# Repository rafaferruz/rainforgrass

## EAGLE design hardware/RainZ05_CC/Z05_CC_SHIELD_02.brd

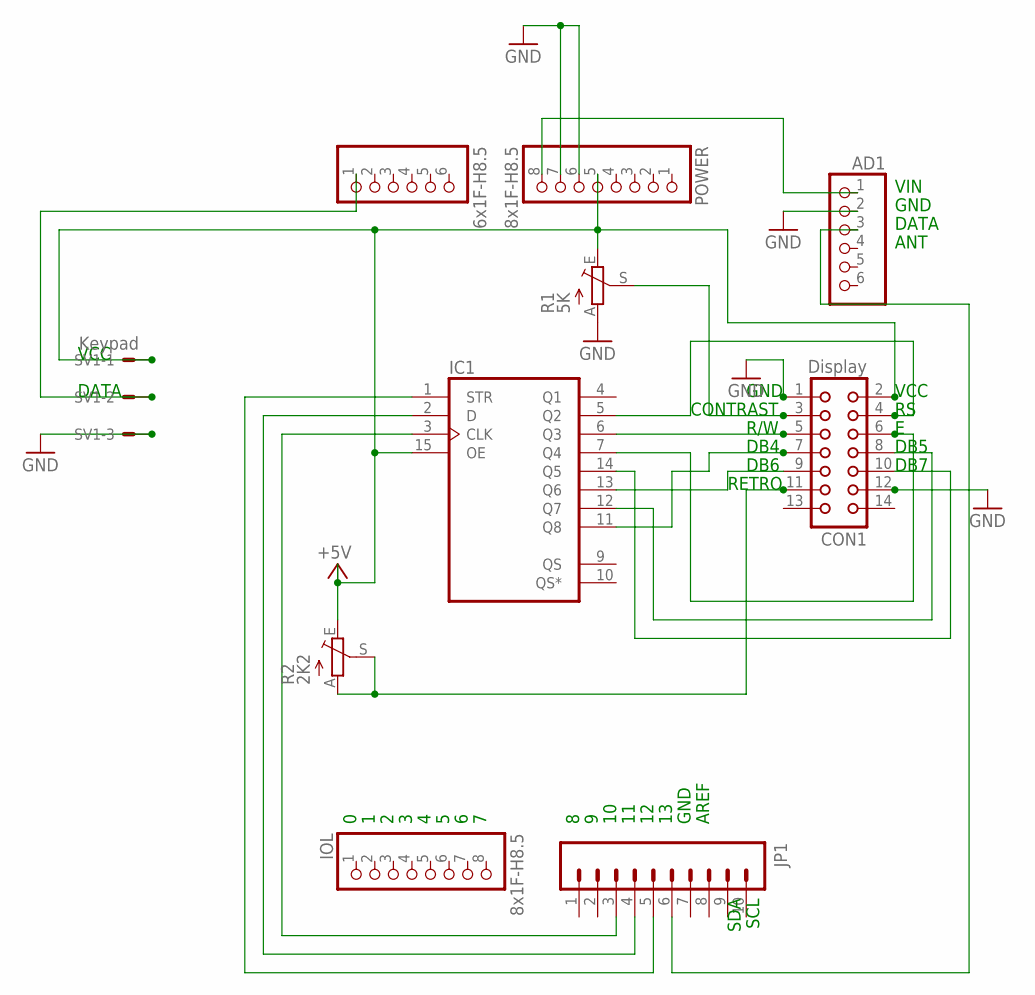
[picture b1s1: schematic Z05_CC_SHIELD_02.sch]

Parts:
AD, AD1: 6x1F-H8.5; 1X06
CON1: Display; CON14
IC1: 4094N; DIL16
IOL: 8x1F-H8.5; 1X08
JP1: M10"; 1X10
POWER: 8x1F-H8.5; 1X08
R1: 5K; LI10
R2: 2K2; LI10
SV1: Keypad; 7395-05

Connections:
+5V: CON1.2, IC1.15 (OE), POWER.5, R1.E, R2.E, SV1.1
A5: AD.1, SV1.2
GND: AD1.2, CON1.1, CON1.12, POWER.6, POWER.7, R1.A, SV1.3
unnamed: CON1.11, R2.A, R2.S
unnamed: AD1.3, JP1.6
unnamed: CON1.3, R1.S
unnamed: IC1.1 (STR), JP1.5
unnamed: IC1.2 (D), JP1.4
unnamed: IC1.3 (CLK), JP1.3
unnamed: CON1.4, IC1.5 (Q2)
unnamed: CON1.5, IC1.6 (Q3)
unnamed: CON1.6, IC1.7 (Q4)
unnamed: CON1.7, IC1.11 (Q8)
unnamed: CON1.8, IC1.12 (Q7)
unnamed: CON1.9, IC1.13 (Q6)
unnamed: CON1.10, IC1.14 (Q5)
VDD: IC1.16 (VDD)
VIN: AD1.1, POWER.8
VSS: IC1.8 (VSS)

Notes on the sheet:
SDA
SCL
GND
AREF
RETRO
VIN
DATA
ANT
VCC
CONTRAST
R/W
DB4
DB5
DB6
DB7

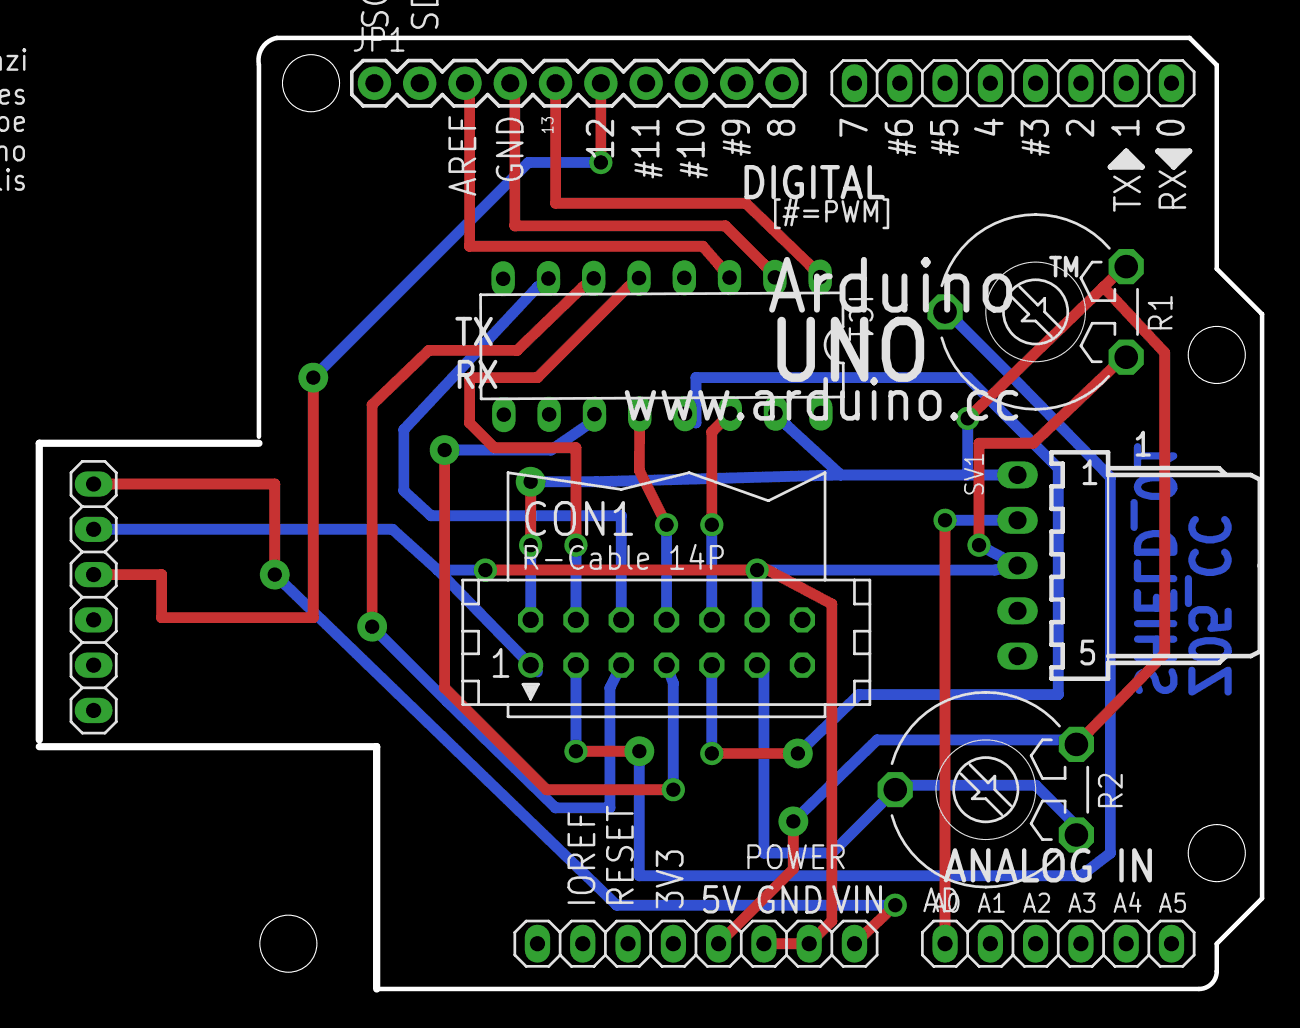
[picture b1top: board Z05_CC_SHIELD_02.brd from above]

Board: 2 copper layers, 68.6 x 53.3 mm, 10 parts (0 on the bottom side), 17 nets.

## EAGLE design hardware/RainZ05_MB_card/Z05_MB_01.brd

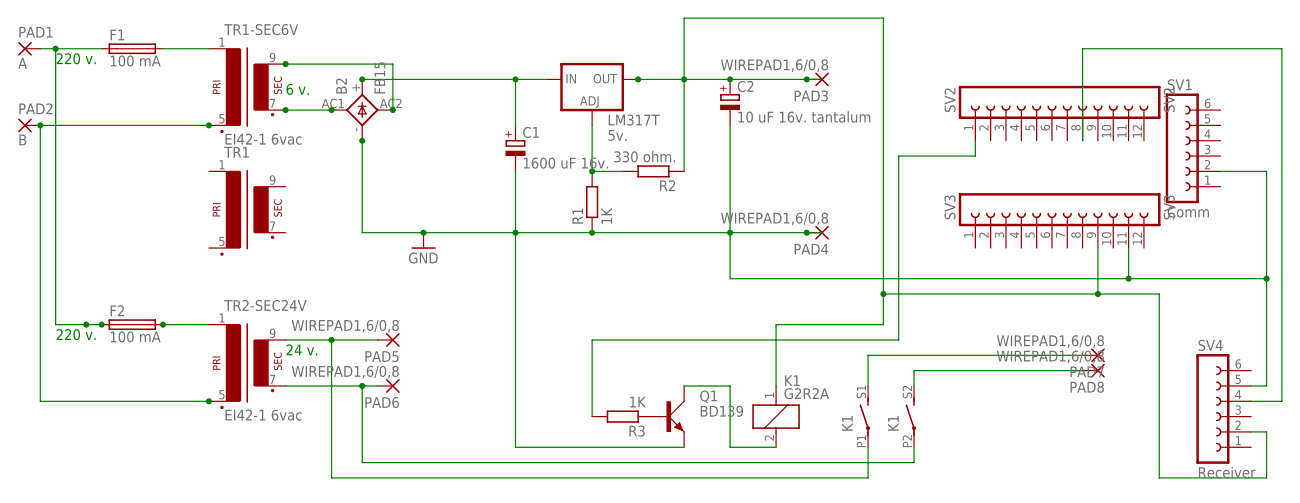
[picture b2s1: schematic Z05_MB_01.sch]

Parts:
B2: FB15
C1: 1600 uF 16v.; E5-13
C2: 10 uF 16v. tantalum; TAP5-60
F1, F2: 100 mA; GSH15
K1: G2R2A
LM317T: 5v.; 317TS
PAD1: A; 2,54/1,1
PAD2: B; 2,54/1,1
PAD3, PAD4, PAD5, PAD6, PAD7, PAD8: WIREPAD1,6/0,8; 1,6/0,8
Q1: BD139; TO126AV
R1, R3: 1K; 0207/12
R2: 330 ohm.; 0207/12
SV1: Comm; FE06
SV2: SV2; FE12
SV3: SV3; FE12
SV4: Receiver; FE06
TR1: EI30-1
TR1-SEC6V, TR2-SEC24V: EI42-1 6vac; EI42-1

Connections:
GND: B2.-, C1.-, C2.-, PAD4.1, Q1.E, R1.1, SV1.2, SV3.11, SV4.5
unnamed: F1.2, TR1-SEC6V.1
unnamed: B2.AC1, TR1-SEC6V.7 (S3)
unnamed: B2.+, C1.+, LM317T.3 (IN)
unnamed: K1.P1, PAD5.1, TR2-SEC24V.9 (S4)
unnamed: C2.+, K1.1, LM317T.2 (OUT), PAD3.1, R2.1, SV3.9, SV4.2
unnamed: LM317T.1 (ADJ), R1.2, R2.2
unnamed: F1.1, F2.1, PAD1.1
unnamed: PAD2.1, TR1-SEC6V.5 (P2), TR2-SEC24V.5 (P2)
unnamed: K1.P2, PAD6.1, TR2-SEC24V.7 (S3)
unnamed: B2.AC2, TR1-SEC6V.9 (S4)
unnamed: F2.2, TR2-SEC24V.1
unnamed: Q1.B, R3.1
unnamed: K1.2, Q1.C
unnamed: K1.S2 (S), PAD8.1
unnamed: K1.S1 (S), PAD7.1
unnamed: R3.2, SV2.1
unnamed: SV2.8, SV4.4

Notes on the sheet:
6 v.
220 v.
24 v.

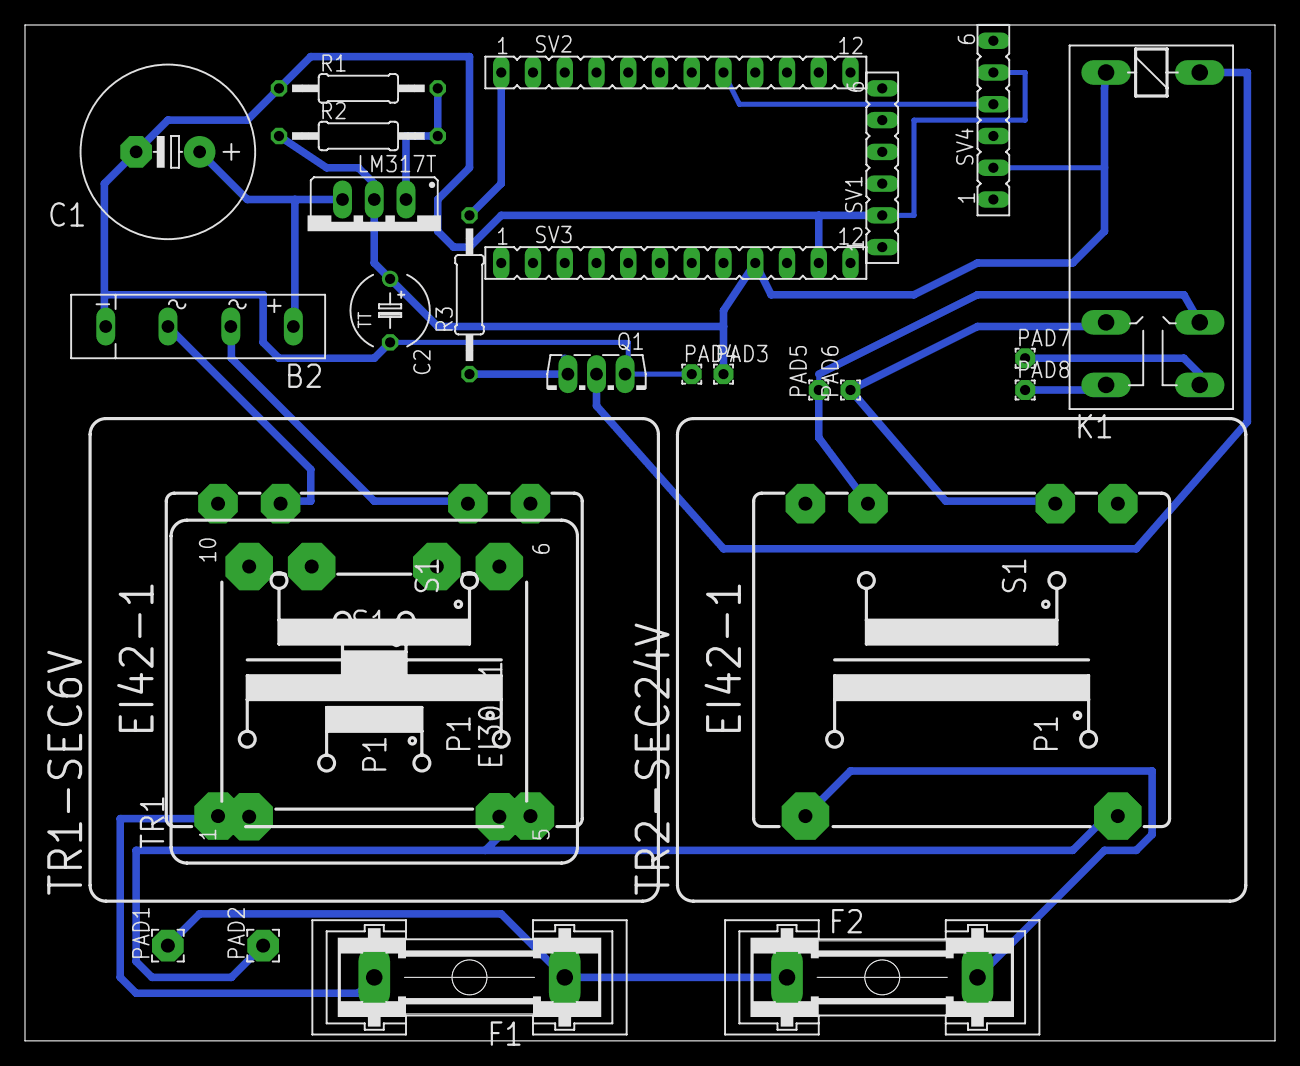
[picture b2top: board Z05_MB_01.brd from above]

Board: 2 copper layers, 100.0 x 81.3 mm, 26 parts (0 on the bottom side), 18 nets.

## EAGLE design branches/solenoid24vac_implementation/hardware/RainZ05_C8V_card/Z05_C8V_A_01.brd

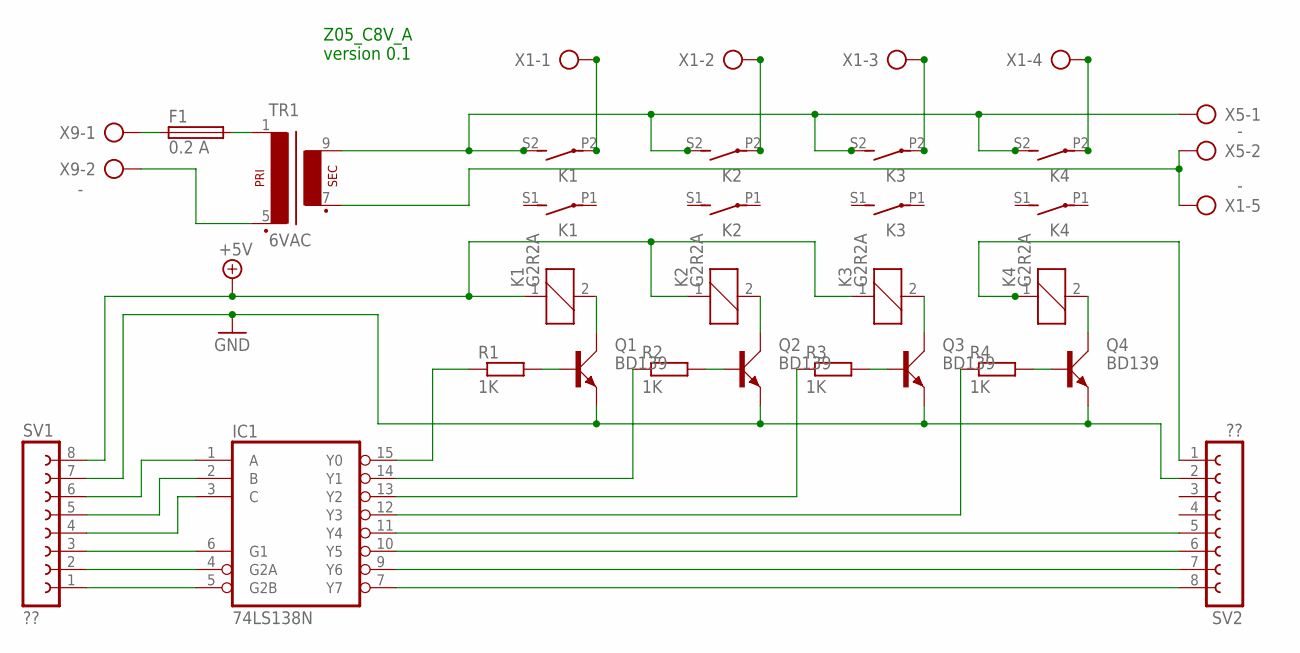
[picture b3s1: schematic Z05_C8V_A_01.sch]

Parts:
F1: 0.2 A; GSH15
IC1: 74LS138N; DIL16
K1, K2, K3, K4: G2R2A
Q1, Q2, Q3, Q4: BD139; TO126AV
R1, R2, R3, R4: 1K; 0204/7
SV1, SV2: ??; FE08W
TR1: 6VAC; EI42-1
X1: -; AK300/5
X5, X9: -; AK300/2

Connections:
+5V: K1.1, K2.1, K3.1, SV1.8
GND: IC1.8 (GND), Q1.E, Q2.E, Q3.E, Q4.E, SV1.7, SV2.2
unnamed: K1.S2 (S), K2.S2 (S), K3.S2 (S), K4.S2 (S), TR1.9 (S4), X5.1
unnamed: TR1.7 (S3), X1.5, X5.2
unnamed: Q1.B, R1.2
unnamed: IC1.15 (Y0), R1.1
unnamed: K1.2, Q1.C
unnamed: K4.1, SV2.1
unnamed: IC1.11 (Y4), SV2.5
unnamed: Q2.B, R2.2
unnamed: K2.2, Q2.C
unnamed: IC1.10 (Y5), SV2.6
unnamed: IC1.9 (Y6), SV2.7
unnamed: Q3.B, R3.2
unnamed: K3.2, Q3.C
unnamed: IC1.7 (Y7), SV2.8
unnamed: Q4.B, R4.2
unnamed: K4.2, Q4.C
unnamed: IC1.14 (Y1), R2.1
unnamed: IC1.13 (Y2), R3.1
unnamed: IC1.12 (Y3), R4.1
unnamed: K1.P2, K2.P2, K3.P2, K4.P2, X1.1, X1.2, X1.3, X1.4
unnamed: F1.1, X9.1
unnamed: F1.2, TR1.1
unnamed: IC1.1 (A), SV1.6
unnamed: IC1.2 (B), SV1.5
unnamed: IC1.3 (C), SV1.4
unnamed: IC1.6 (G1), SV1.3
unnamed: IC1.4 (G2A), SV1.2
unnamed: IC1.5 (G2B), SV1.1
unnamed: TR1.5 (P2), X9.2
VCC: IC1.16 (VCC)

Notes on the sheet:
Z05_C8V_A version 0.1

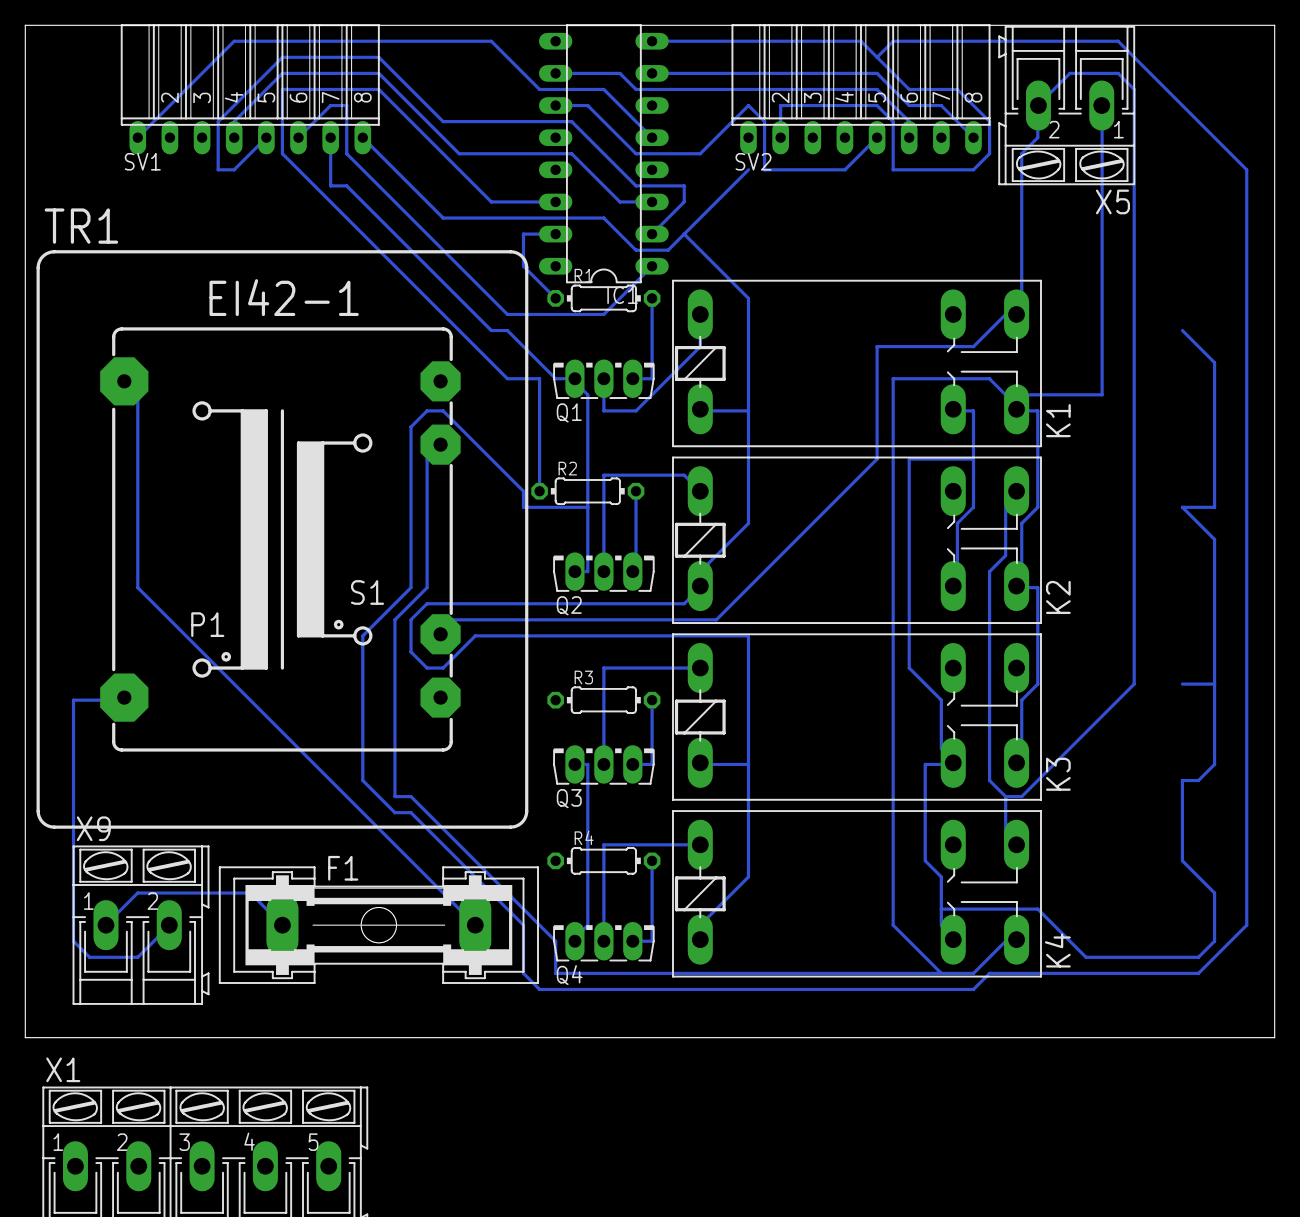
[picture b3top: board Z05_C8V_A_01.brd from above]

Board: 2 copper layers, 98.7 x 80.0 mm, 20 parts (0 on the bottom side), 31 nets.

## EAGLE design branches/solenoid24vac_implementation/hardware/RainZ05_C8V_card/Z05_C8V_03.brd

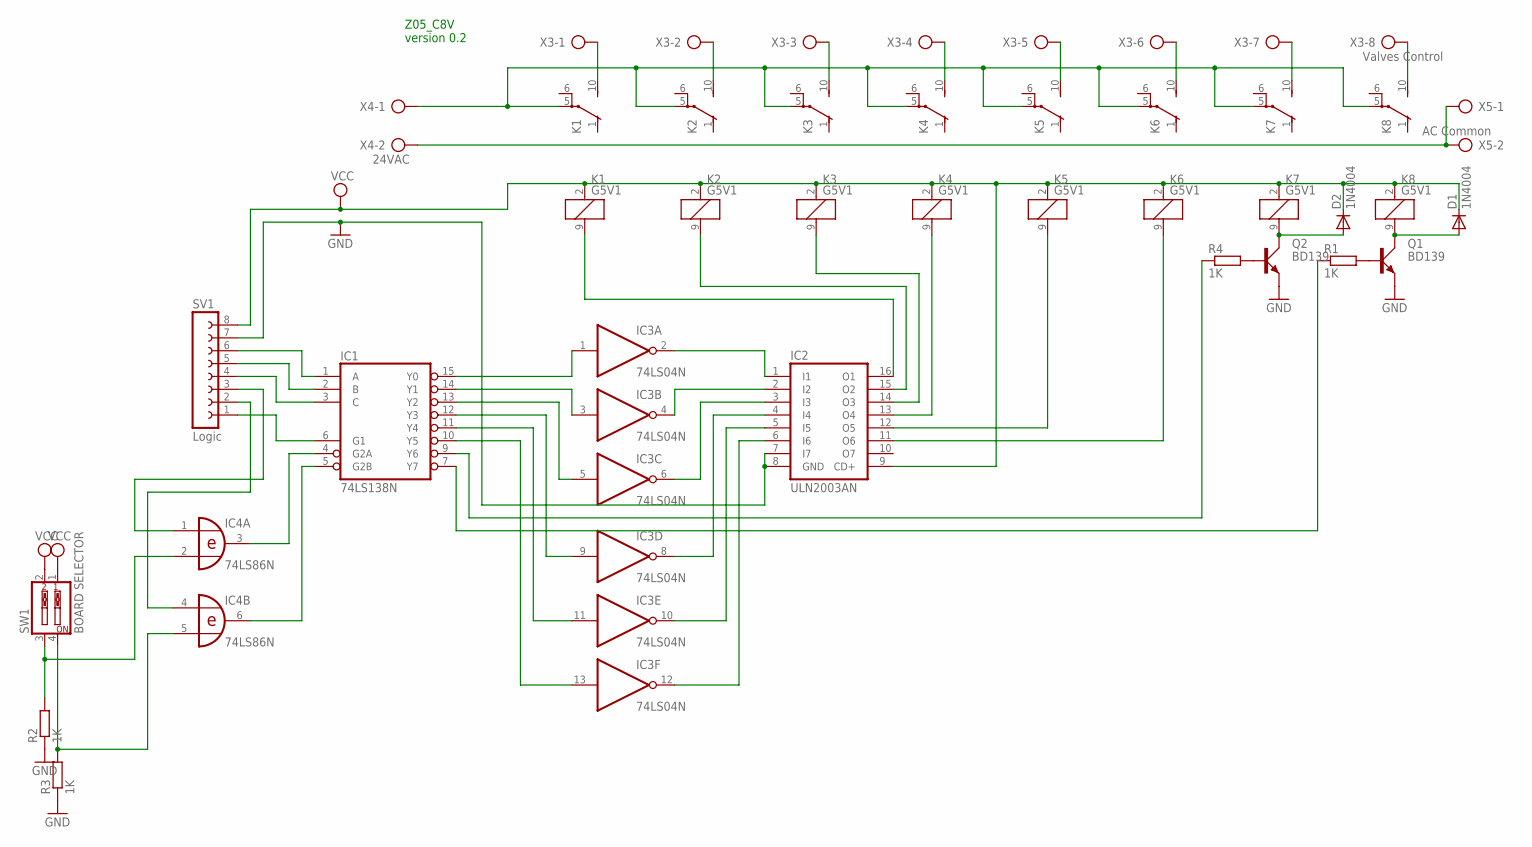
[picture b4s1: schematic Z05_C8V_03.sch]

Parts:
D1, D2: 1N4004; DO41-10
IC1: 74LS138N; DIL16
IC2: ULN2003AN; DIL16
IC3: 74LS04N; DIL14
IC4: 74LS86N; DIL14
K1, K2, K3, K4, K5, K6, K7, K8: G5V1
Q1, Q2: BD139; TO126AV
R1, R2, R3, R4: 1K; 0204/7
SV1: Logic; FE08
SW1: BOARD SELECTOR; EDG-02
X3: Valves Control; AK500/8
X4: 24VAC; AK500/2
X5: AC Common; AK500/2

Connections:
GND: IC1.8 (GND), IC2.7 (I7), IC2.8 (GND), IC3.7 (GND), IC4.7 (GND), Q1.E, Q2.E, R2.1, R3.1, SV1.7
unnamed: IC2.15 (O2), K2.9 (2)
unnamed: IC1.15 (Y0), IC3.1 (I)
unnamed: IC1.14 (Y1), IC3.3 (I)
unnamed: IC1.13 (Y2), IC3.5 (I)
unnamed: IC1.12 (Y3), IC3.9 (I)
unnamed: IC1.11 (Y4), IC3.11 (I)
unnamed: IC1.10 (Y5), IC3.13 (I)
unnamed: K1.5, K2.5, K3.5, K4.5, K5.5, K6.5, K7.5, K8.5, X4.1
unnamed: IC4.1 (I0), SV1.3
unnamed: X4.2, X5.1, X5.2
unnamed: K1.10 (S), X3.1
unnamed: K2.10 (S), X3.2
unnamed: K3.10 (S), X3.3
unnamed: K4.10 (S), X3.4
unnamed: K5.10 (S), X3.5
unnamed: K6.10 (S), X3.6
unnamed: K7.10 (S), X3.7
unnamed: K8.10 (S), X3.8
unnamed: IC4.4 (I0), SV1.2
unnamed: D1.A, K8.9 (2), Q1.C
unnamed: IC2.16 (O1), K1.9 (2)
unnamed: Q1.B, R1.2
unnamed: IC1.7 (Y7), R1.1
unnamed: IC2.14 (O3), K3.9 (2)
unnamed: IC2.13 (O4), K4.9 (2)
unnamed: IC2.12 (O5), K5.9 (2)
unnamed: IC2.11 (O6), K6.9 (2)
unnamed: IC1.9 (Y6), R4.1
unnamed: D2.A, K7.9 (2), Q2.C
unnamed: IC4.5 (I1), R3.2, SW1.4
unnamed: IC1.4 (G2A), IC4.3 (O)
unnamed: IC1.5 (G2B), IC4.6 (O)
unnamed: IC4.2 (I1), R2.2, SW1.3
unnamed: IC2.1 (I1), IC3.2 (O)
unnamed: IC2.2 (I2), IC3.4 (O)
unnamed: IC2.3 (I3), IC3.6 (O)
unnamed: IC2.4 (I4), IC3.8 (O)
unnamed: IC2.5 (I5), IC3.10 (O)
unnamed: IC2.6 (I6), IC3.12 (O)
unnamed: Q2.B, R4.2
unnamed: IC1.1 (A), SV1.6
unnamed: IC1.2 (B), SV1.5
unnamed: IC1.3 (C), SV1.4
unnamed: IC1.6 (G1), SV1.1
VCC: D1.C, D2.C, IC1.16 (VCC), IC2.9 (CD+), IC3.14 (VCC), IC4.14 (VCC), K1.2 (1), K2.2 (1), K3.2 (1), K4.2 (1), K5.2 (1), K6.2 (1), K7.2 (1), K8.2 (1), SV1.8, SW1.1, SW1.2

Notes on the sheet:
Z05_C8V version 0.2

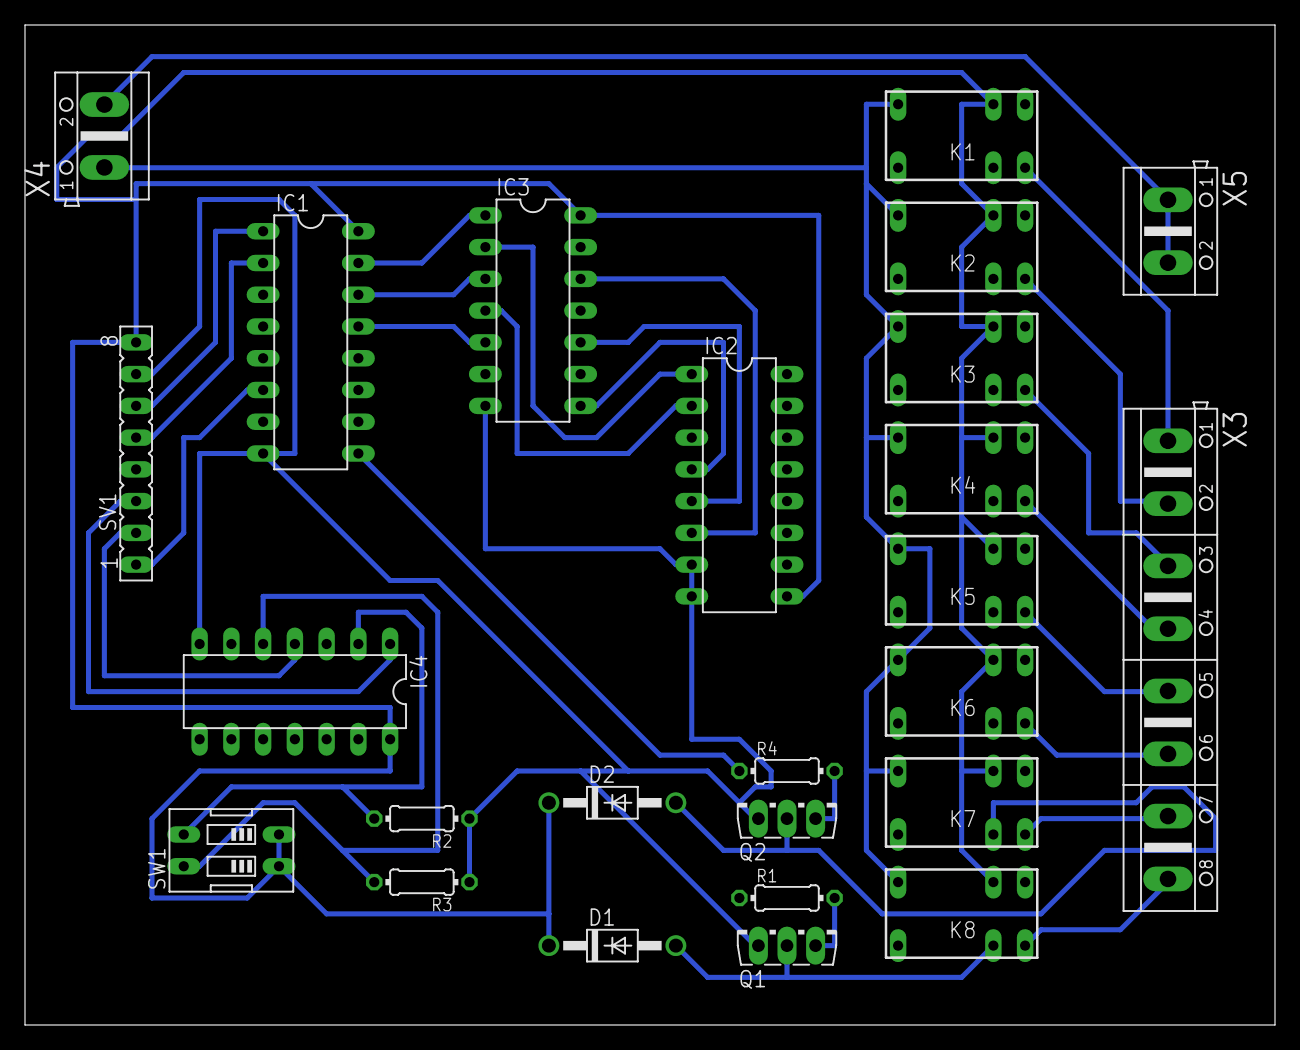
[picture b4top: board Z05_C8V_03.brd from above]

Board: 2 copper layers, 100.0 x 80.0 mm, 25 parts (0 on the bottom side), 46 nets.

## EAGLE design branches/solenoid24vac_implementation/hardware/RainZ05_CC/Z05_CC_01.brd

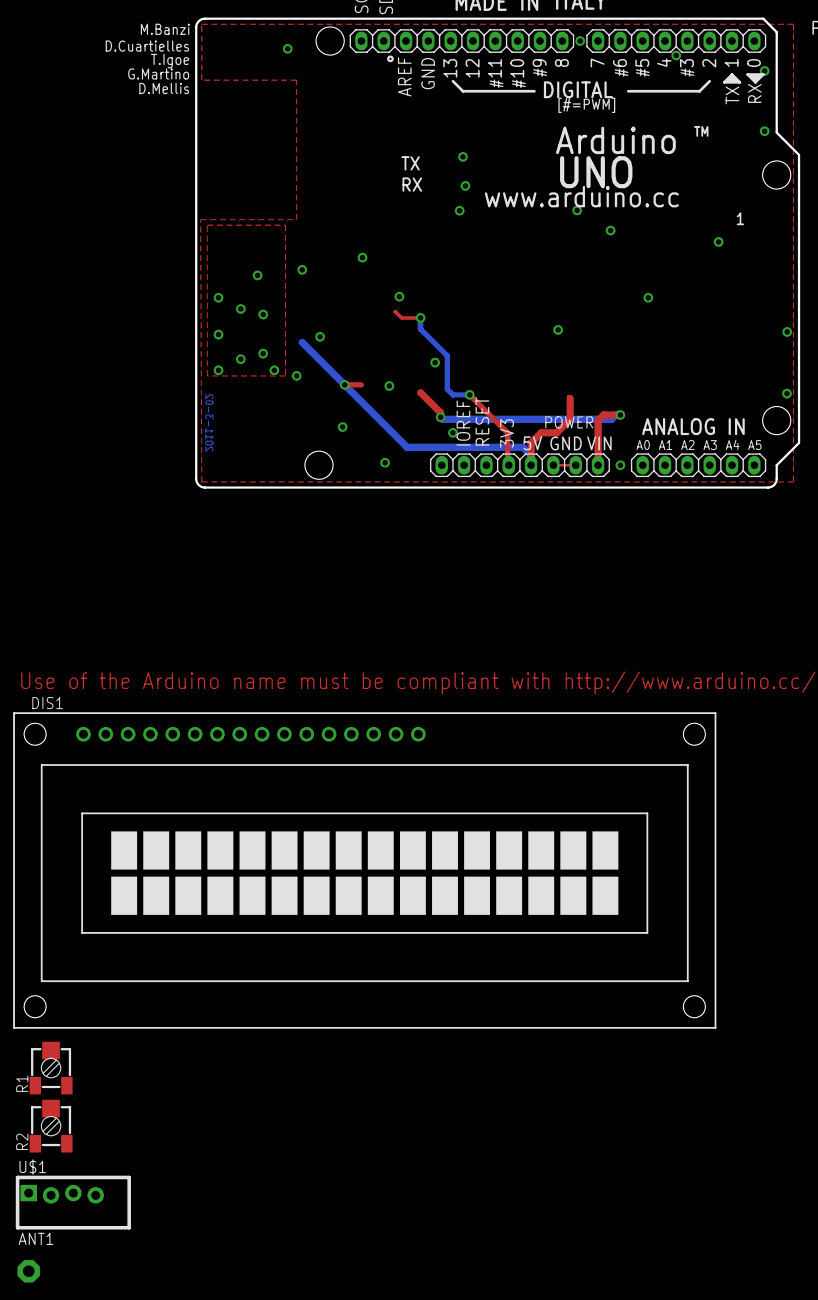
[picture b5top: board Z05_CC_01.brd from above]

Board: 2 copper layers, 68.6 x 53.3 mm, 9 parts (0 on the bottom side), 12 nets.

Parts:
AD: 6x1F-H8.5; 1X06
ANT1: PAD-01
DIS1: TUXGR_16X2_R2
IOH: 10x1F-H8.5; 1X10@1
IOL: 8x1F-H8.5; 1X08
POWER: 8x1F-H8.5; 1X08
R1, R2: RTRIM3314J
U$1: RF-LINK_TX

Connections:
+5V: DIS1.2, POWER.5, R1.1, R2.1, U$1.VCC
A0: AD.6, DIS1.11
A1: AD.5, DIS1.12
A2: AD.4, DIS1.13
A3: AD.3, DIS1.14
A4: AD.2, DIS1.6
A5: AD.1, DIS1.4
GND: DIS1.1, POWER.6, POWER.7, R1.3, U$1.GND
unnamed: DIS1.3, R1.2
unnamed: DIS1.15, R2.2, R2.3
unnamed: IOH.6, U$1.DATA
unnamed: ANT1.1, U$1.ANT

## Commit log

2012-08-13 Initial directory structure.
2012-08-14 Upload inicial
2012-08-14 modificaciones puesta en marcha
2012-08-17 versión final 0.0
2012-10-11 Primera revisión de la versión 01
2012-10-12 Crear directorio z01
2012-10-12 Separar en directorios de versiones
2012-10-17 Modificaciones versión 01
2012-10-18 Correcciones de fallos de entrada de datos por keypad
2012-10-22 Modificaciones en z01 fase 2
2012-10-22 Añadidos directorios que faltaban
2012-10-23 Ultimas Modificaciones en z01 fase 2. Final Fase 2.
2012-10-26 Inicio versión z02
2012-10-28 Inclusión de librerías VirtualWire y RainPComm
2012-10-31 Final de la Fase 3. Actualización de clases y documentación.
2012-10-31 Inicio version z03.
2012-11-04 Primera versión del receptor
2012-11-11 Primera versión operativa de comunicaciones emisión recepción
2012-11-12 Lograda comunicación entre emisor receptor
2012-11-12 z04r librerías y ficheros que faltaban en el repositorio
2012-11-13 Salvar trabajo día z04r
2012-11-14 z04r ya funciona. Guardar trabajo día
2012-11-28 Subiendo versión z05
2012-11-28 Subiendo librerias
2012-11-28 Subiendo librerias que faltaban
2012-11-28 Subiendo fichero longitud antenas
2012-11-28 Subiendo TextInput y modificaciones del día
2012-11-29 Guardar trabajo día.
2012-11-29 Crear rama para implementación de inputs de fechas y horas.
2012-11-30 Implementación de comprobaciones de datos entrados mediante patrones de datos. Incorporación de librerias para manipulación de fechas y horas.
2012-12-01 Implementación chequeo de fecha y hora
2013-01-14 Añadido solenoid 24vac
2013-02-11 Para ver en qué rama estoy
2013-02-11 Incluye solenoid24vac
2013-02-11 Creando rama para solenoid24vac
2013-03-25 Modificación fichero documentación
2013-03-26 Inclusión del directorio que contiene los ficheros de diseño hardware
2013-03-26 Eliminacion del repositorio del directorio que contiene los ficheros de diseño hardware
2014-02-25 Creación carpeta docs para guardar la documentación de la versión
2014-02-25 Borrado de documentos de la carpeta z05
2014-03-10 Implementación de objetos de la aplicacion
2014-04-09 Se ha finalizado la refactorización de todos los ficheros que intervienen en el sketchbook rain_z05_controller
2014-04-12 Puesta en marcha del controlador de la etapa de potencia.\nModificaciones del protocolo RainPComm para asegurar las comunicaciones.
2014-08-23 Nueva placa shield arduino para gestionar teclado y display en modo serie
2014-08-24 Modificaciones en diámetro de vías y posición de algunas pistas
2014-08-24 Modificación parámetrso impresión placa
2014-08-30 Commiting por si hay algo pendiente que no recuerdo
2015-05-16 Migrating wiki contents from Google Code

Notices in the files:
parts and their libraries:
SparkFun-RF: Licensing: CC v3.0 Share-Alike You are welcome to use this library for commercial purposes.
